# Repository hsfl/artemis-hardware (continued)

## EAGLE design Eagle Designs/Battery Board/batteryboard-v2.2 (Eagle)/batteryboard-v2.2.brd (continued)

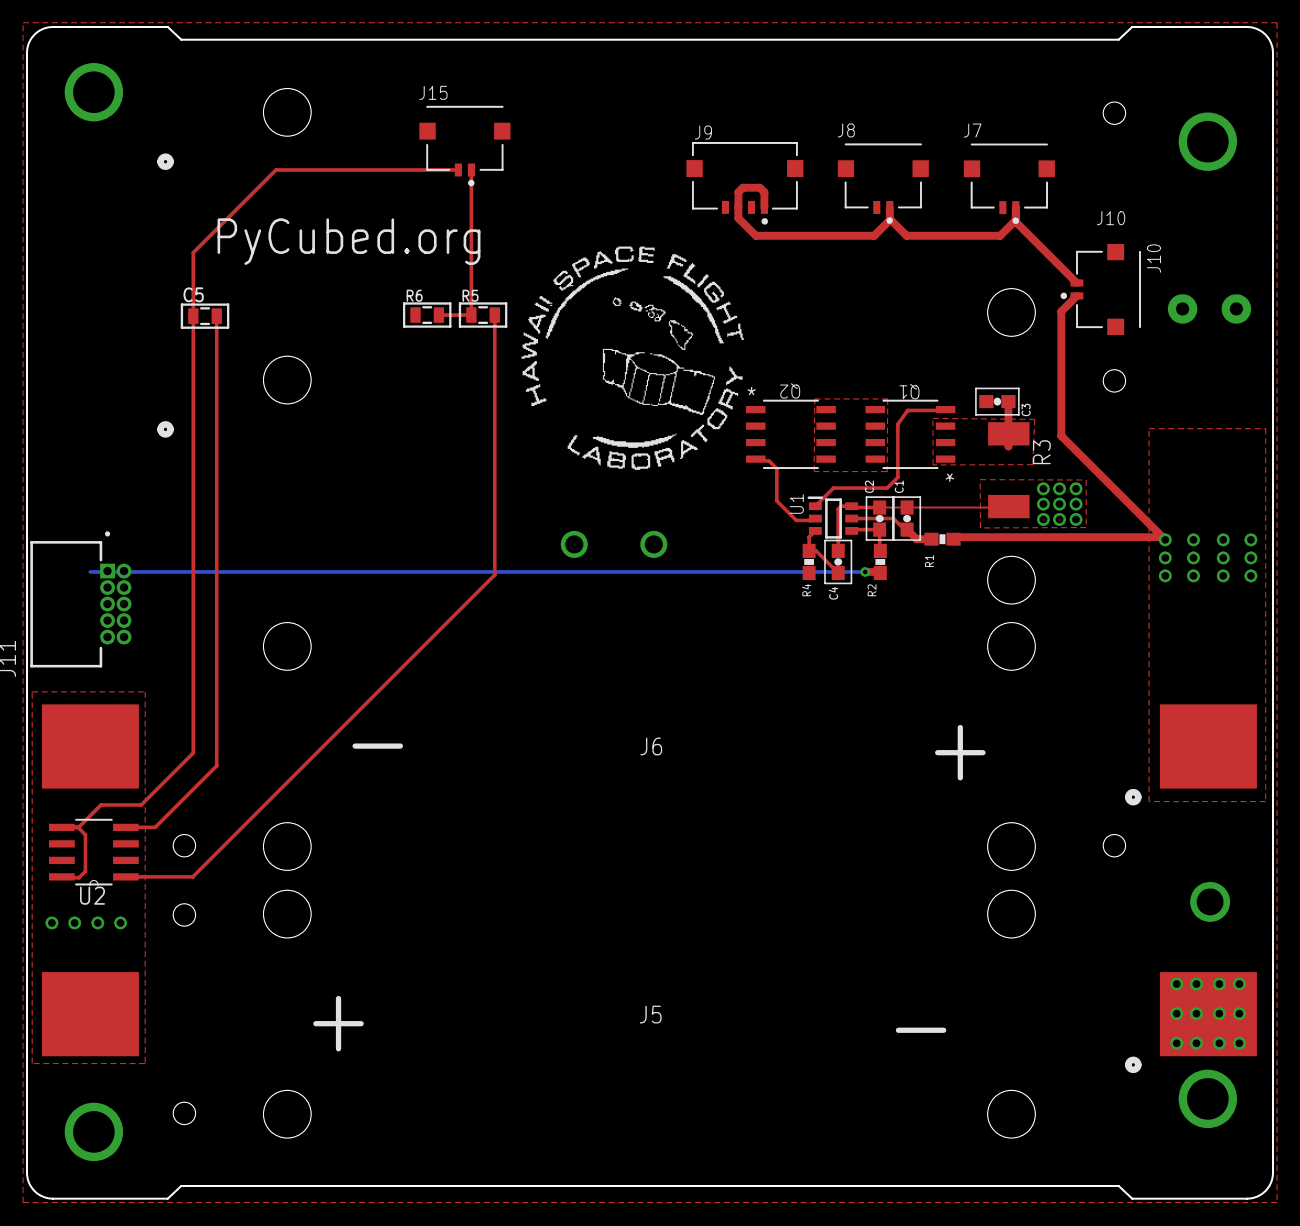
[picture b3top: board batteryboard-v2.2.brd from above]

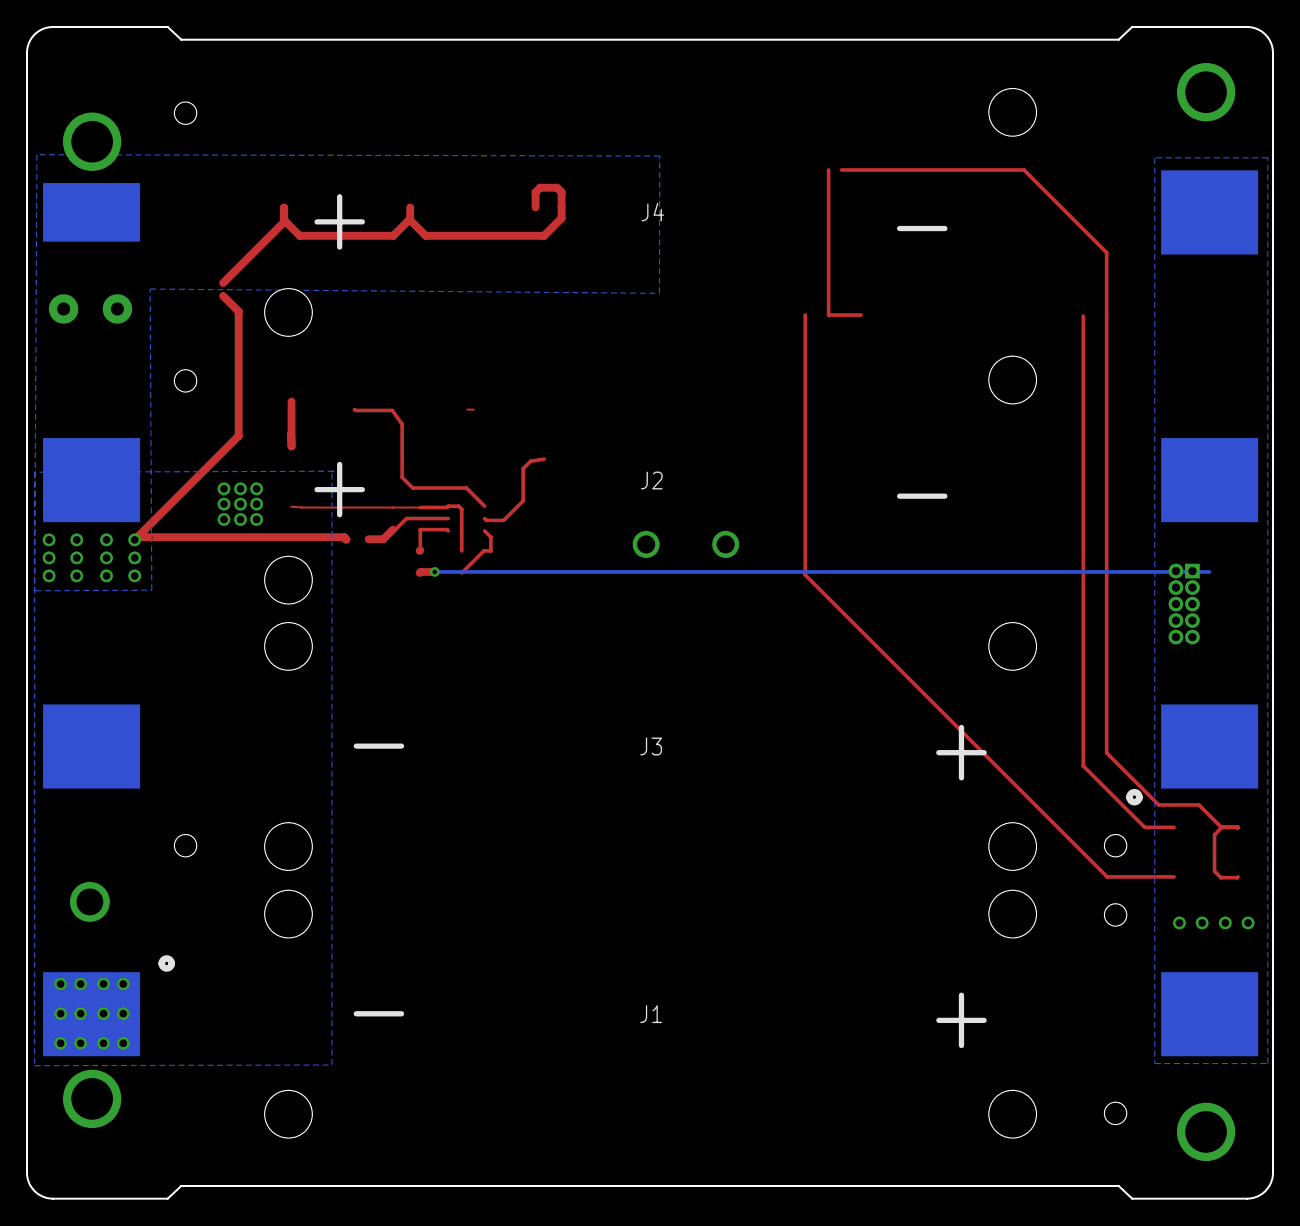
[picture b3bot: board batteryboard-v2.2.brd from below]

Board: 2 copper layers, 95.9 x 90.2 mm, 28 parts (4 on the bottom side), 16 nets.

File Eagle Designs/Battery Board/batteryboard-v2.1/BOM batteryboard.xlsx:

Id | Designator | Package | Quantity | Designation | Supplier and ref | Column1 | _1
1 | R6 | R_0805_2012Metric | 1 | 10k
2 | R5 | R_0805_2012Metric | 1 | 45.3k
3 | J2,J4,J6,J5,J3,J1 | KEYSTONE-1042 | 6 | KEYSTONE-1042
4 | Ref** | battery_version | 1 | Val**
5 | H3,H4,H2,H1 | MountingHole_3.2mm_M3_DIN965_PadMOD | 4 | MountingHole_Pad
6 | Ref** | pycubed_logo | 1 | Val**
7 | REF**,REF**,REF**,REF**,REF**,REF** | Fiducial_0.75mm_Mask1.5mm | 6 | Fiducial_0.75mm_Mask1.5mm
8 | TH1 | R_Axial_DIN0204_L3.6mm_D1.6mm_P5.08mm_Vertical | 1 | Thermistor
9 | J12 | PinHeader_1x01_P1.00mm_Vertical | 1 | Screw_Terminal_01x01
10 | TP4,TP3,TP2,TP1 | TestPoint_Loop_D1.80mm_Drill1.0mm_Beaded | 4 | TestPoint
11 | C3,C4,C2,C1,C5 | C_0603_1608Metric | 4 | 0.1uF
12 | R4 | R_0603_1608Metric | 1 | 1K
13 | R2,R1 | R_0603_1608Metric | 2 | 330
14 | R3 | R_2512_6332Metric | 1 | 0.01
15 | Q2,Q1 | SOIC-8_3.9x4.9mm_P1.27mm | 2 | IRF7458
16 | U1 | SOT95P280X130-6N | 1 | R5460N233AF
17 | J7,J8,J10 | Molex_Pico-Lock_503763-0291_1x02-1MP_P1.00m_Horizontal | 3 | Conn_01x02_Female
18 | J9,J11 | Molex_Pico-Lock_503763-0491_1x04-1MP_P1.00mm_Horizontal | 2 | Conn_01x04_Female
19 | U2 | TMP36FSZ-REEL | 1 | TMP36FSZ-REEL

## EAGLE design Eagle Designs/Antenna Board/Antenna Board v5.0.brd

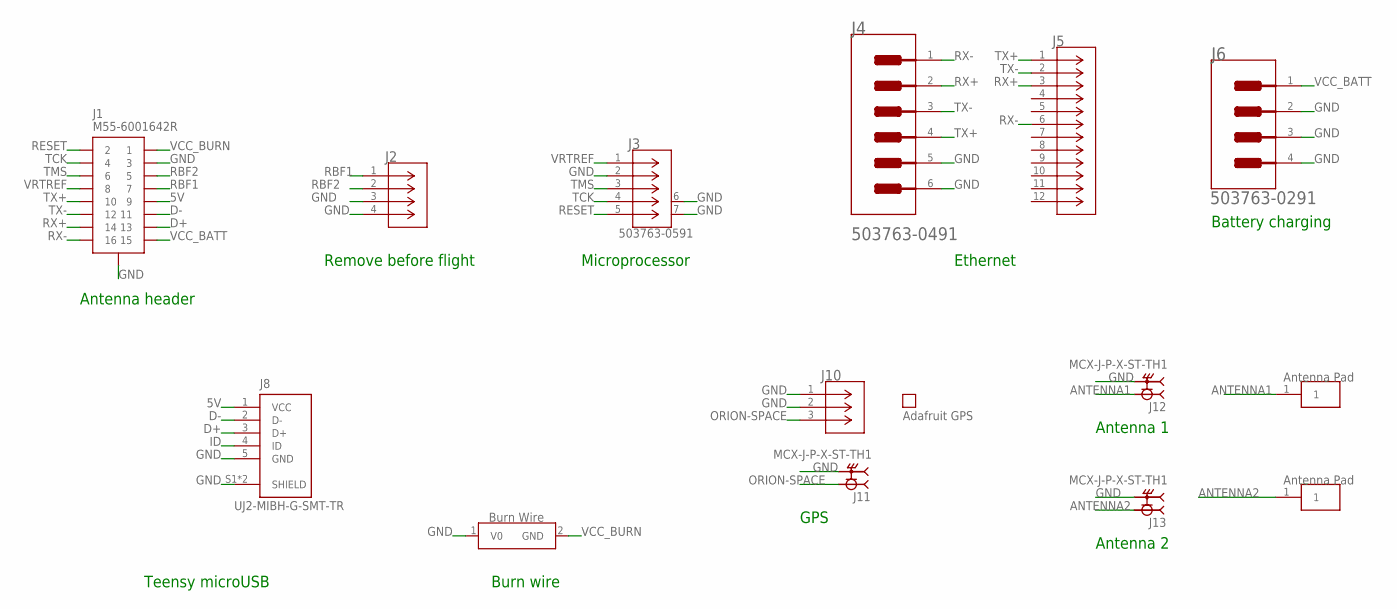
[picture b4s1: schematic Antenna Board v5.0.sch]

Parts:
GPS: PA1010D
J1: M55-6001642R; CONN_M55-6001642R_HRW
J2: 5037630291; CON_5037630291
J3: 503763-0591; CONN_5037630591_MOL
J4: MOLEX_503763-0491MOLEX_503763-0491_0_0; MOLEX_503763-0491_0
J5: ARJM11C7-104-AB-EW2; CONN_EW_ABR
J6: MOLEX_503763-0291MOLEX_503763-0291_0_0; MOLEX_503763-0291_0
J8: UJ2-MIBH-G-SMT-TR; CUI_UJ2-MIBH-G-SMT-TR
J10: U.FL-R-SMT-1(01); CONN_-SMT-1(01)
J11, J12, J13: MCX-J-P-X-ST-TH1; SAMTEC_MCX-J-P-X-ST-TH1
U$1, U$2: ANTENNA_PAD
U$3: BURNWIRE

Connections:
5V: J1.9, J8.1 (VCC)
ANTENNA1: J12.1, U$2.1
ANTENNA2: J13.1, U$1.1
D+: J1.13, J8.3 (D+)
D-: J1.11, J8.2 (D-)
GND: J1.3, J1.19 (GND), J1.20 (GND), J1.21 (GND), J1.22 (GND), J2.3, J2.4, J3.2, J3.6, J3.7, J4.5 (MNT_1), J4.6 (MNT_2), J6.2, J6.3 (MNT_1), J6.4 (MNT_2), J8.5 (GND), J8.S1 (SHIELD), J8.S2 (SHIELD), J10.1, J10.2, J11.S1 (2), J11.S2 (2), J11.S3 (2), J11.S4 (2), J12.S1 (2), J12.S2 (2), J12.S3 (2), J12.S4 (2), J13.S1 (2), J13.S2 (2), J13.S3 (2), J13.S4 (2), U$3.1 (V0)
ID: J8.4 (ID)
ORION-SPACE: J10.3, J11.1
RBF1: J1.7, J2.1
RBF2: J1.5, J2.2
RESET: J1.2, J3.5
RX+: J1.14, J4.2, J5.3
RX-: J1.16, J4.1, J5.6
TCK: J1.4, J3.4
TMS: J1.6, J3.3
TX+: J1.10, J4.4, J5.1
TX-: J1.12, J4.3, J5.2
VCC_BATT: J1.15, J6.1
VCC_BURN: J1.1, U$3.2 (GND)
VRTREF: J1.8, J3.1

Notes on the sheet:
Remove before flight
Microprocessor
Battery charging
Teensy microUSB
Burn wire
GPS
Antenna 1
Antenna 2
Ethernet
Antenna header

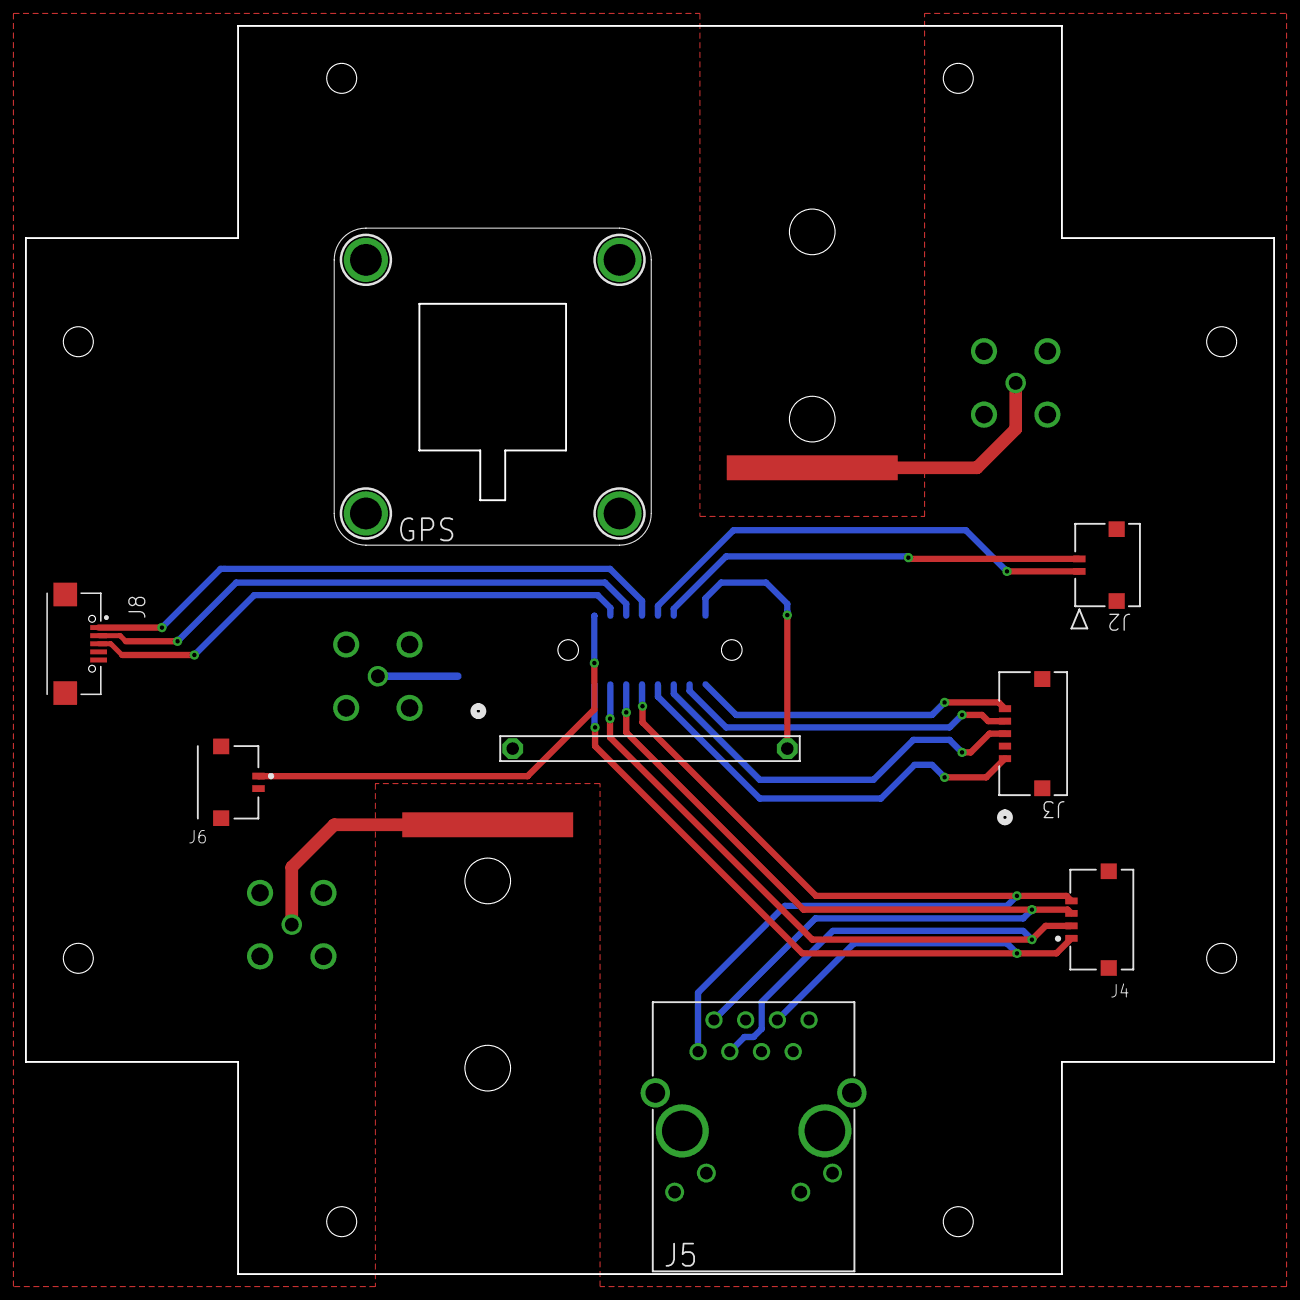
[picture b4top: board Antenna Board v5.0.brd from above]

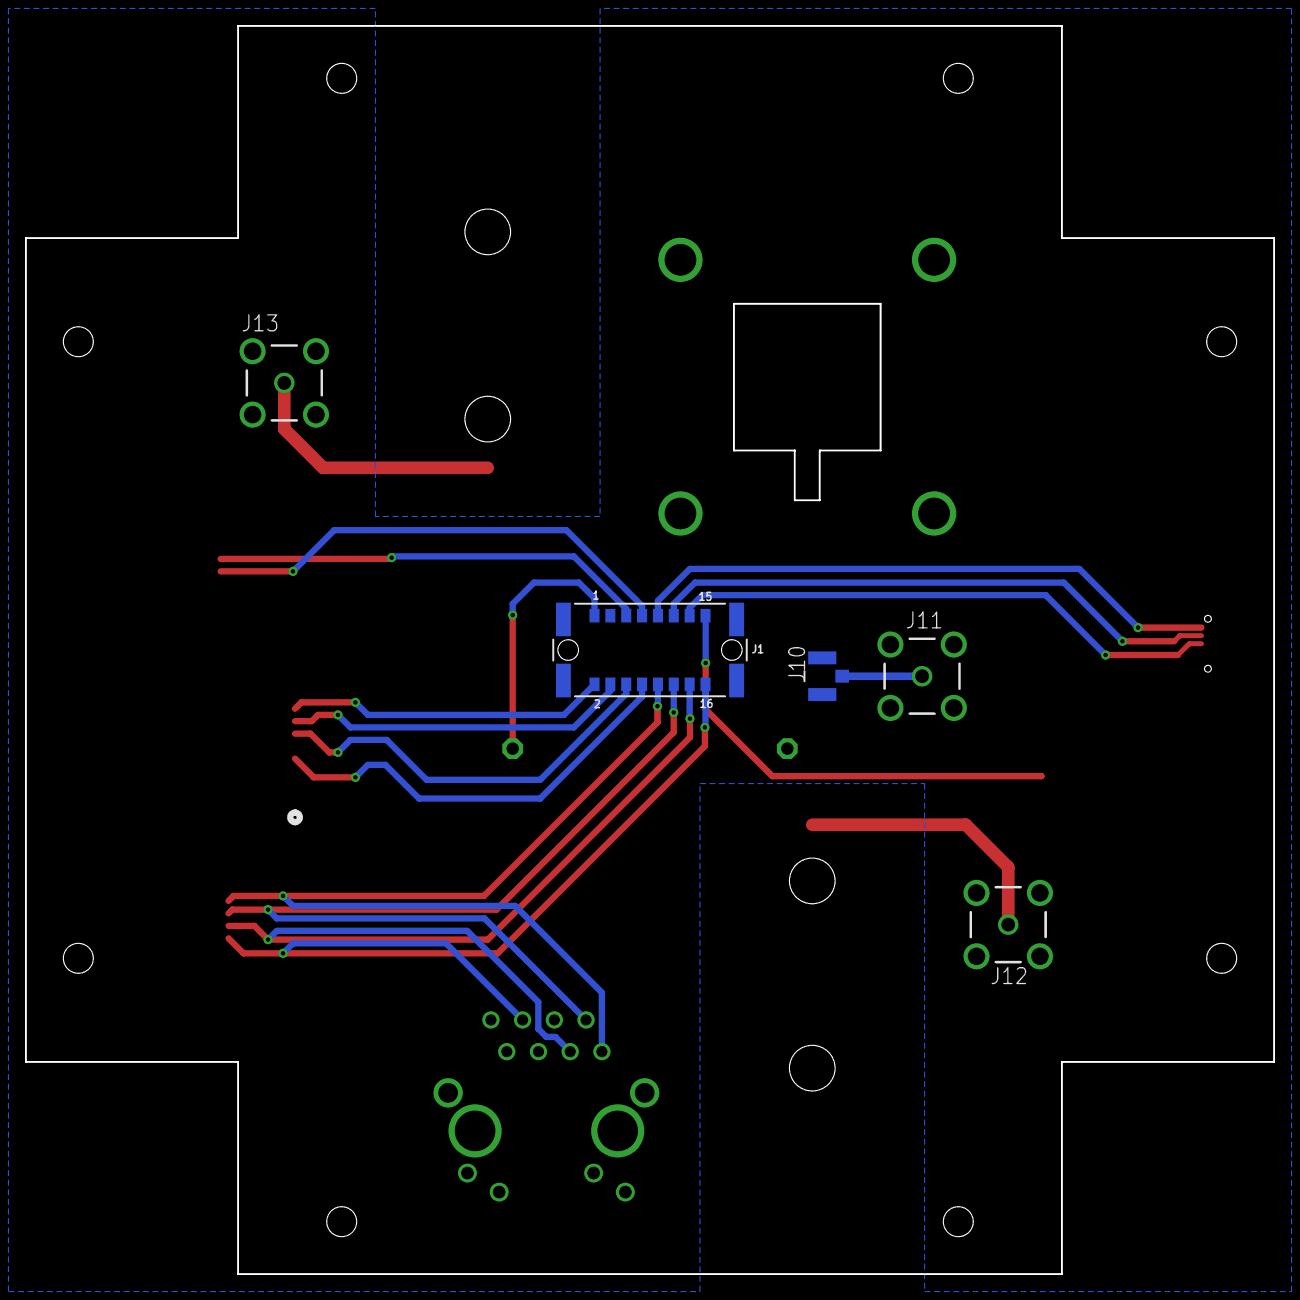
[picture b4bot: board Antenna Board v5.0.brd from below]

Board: 2 copper layers, 100.0 x 100.0 mm, 15 parts (5 on the bottom side), 19 nets.

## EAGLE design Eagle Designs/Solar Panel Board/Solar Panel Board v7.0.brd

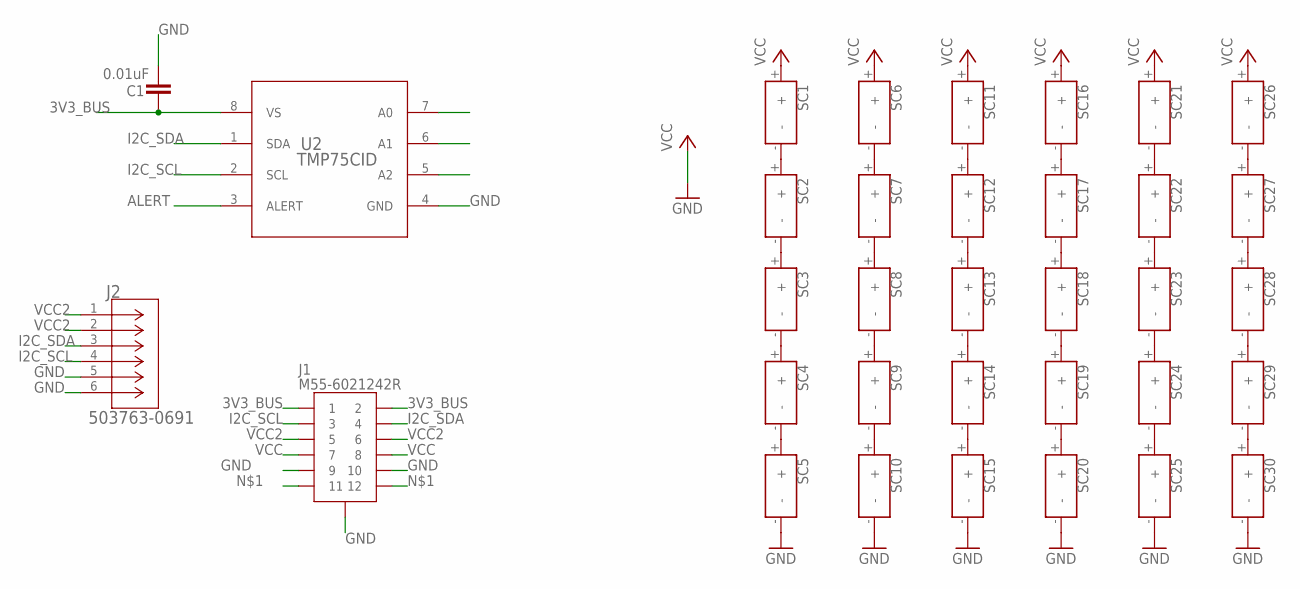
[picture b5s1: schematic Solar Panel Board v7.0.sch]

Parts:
C1: 0.01uF; 0805
J1: M55-6021242R
J2: 503763-0691; CONN_503763-0691_MOL
SC1, SC2, SC3, SC4, SC5, SC6, SC7, SC8, SC9, SC10, SC11, SC12, SC13, SC14, SC15, SC16, SC17, SC18, SC19, SC20, SC21, SC22, SC23, SC24, SC25, SC26, SC27, SC28, SC29, SC30: KXOB25-05X3F
U2: TMP75CID; D0008A_N

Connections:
3V3_BUS: C1.1, J1.1, J1.2, U2.8 (VS)
ALERT: U2.3 (ALERT)
GND: C1.2, J1.9, J1.10, J1.P$1 (GND), J1.P$2 (GND), J1.P$3 (GND), J1.P$4 (GND), J2.5, J2.6, SC5.-, SC10.-, SC15.-, SC20.-, SC25.-, SC30.-, U2.4 (GND)
I2C_SCL: J1.3, J2.4, U2.2 (SCL)
I2C_SDA: J1.4, J2.3, U2.1 (SDA)
unnamed: J1.11, J1.12
unnamed: SC7.-, SC8.+
unnamed: SC4.-, SC5.+
unnamed: SC3.-, SC4.+
unnamed: SC2.-, SC3.+
unnamed: SC1.-, SC2.+
unnamed: SC8.-, SC9.+
unnamed: SC16.-, SC17.+
unnamed: SC14.-, SC15.+
unnamed: SC13.-, SC14.+
unnamed: SC9.-, SC10.+
unnamed: SC11.-, SC12.+
unnamed: SC23.-, SC24.+
unnamed: SC22.-, SC23.+
unnamed: SC21.-, SC22.+
unnamed: SC6.-, SC7.+
unnamed: SC17.-, SC18.+
unnamed: SC19.-, SC20.+
unnamed: SC12.-, SC13.+
unnamed: SC28.-, SC29.+
unnamed: SC29.-, SC30.+
unnamed: SC26.-, SC27.+
unnamed: SC24.-, SC25.+
unnamed: SC18.-, SC19.+
unnamed: SC27.-, SC28.+
VCC: J1.7, J1.8, SC1.+, SC6.+, SC11.+, SC16.+, SC21.+, SC26.+
VCC2: J1.5, J1.6, J2.1, J2.2

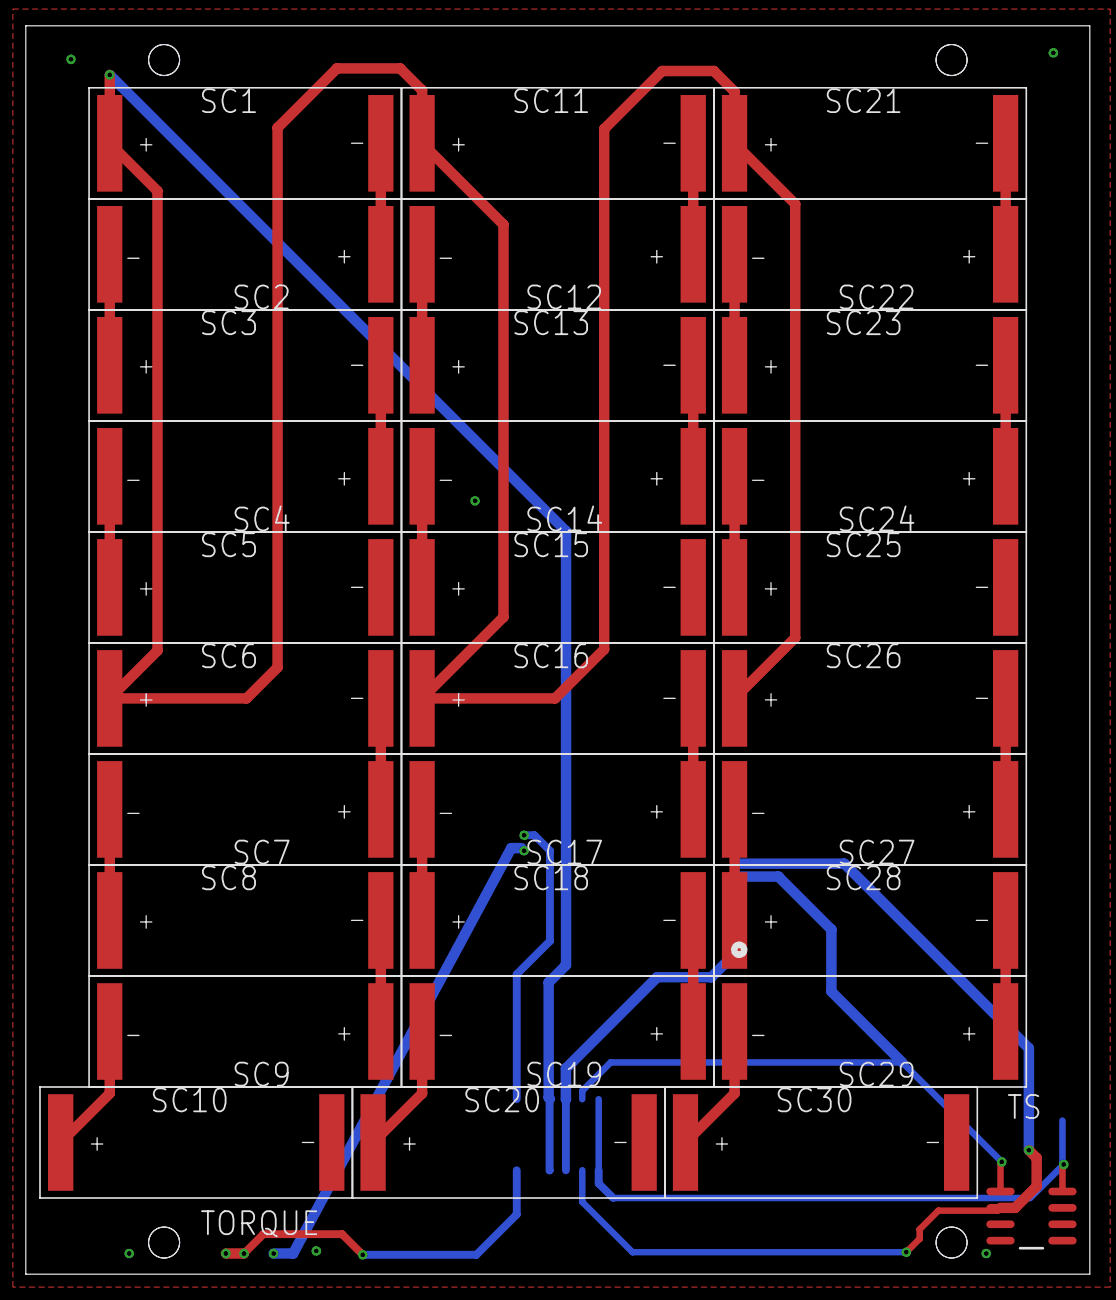
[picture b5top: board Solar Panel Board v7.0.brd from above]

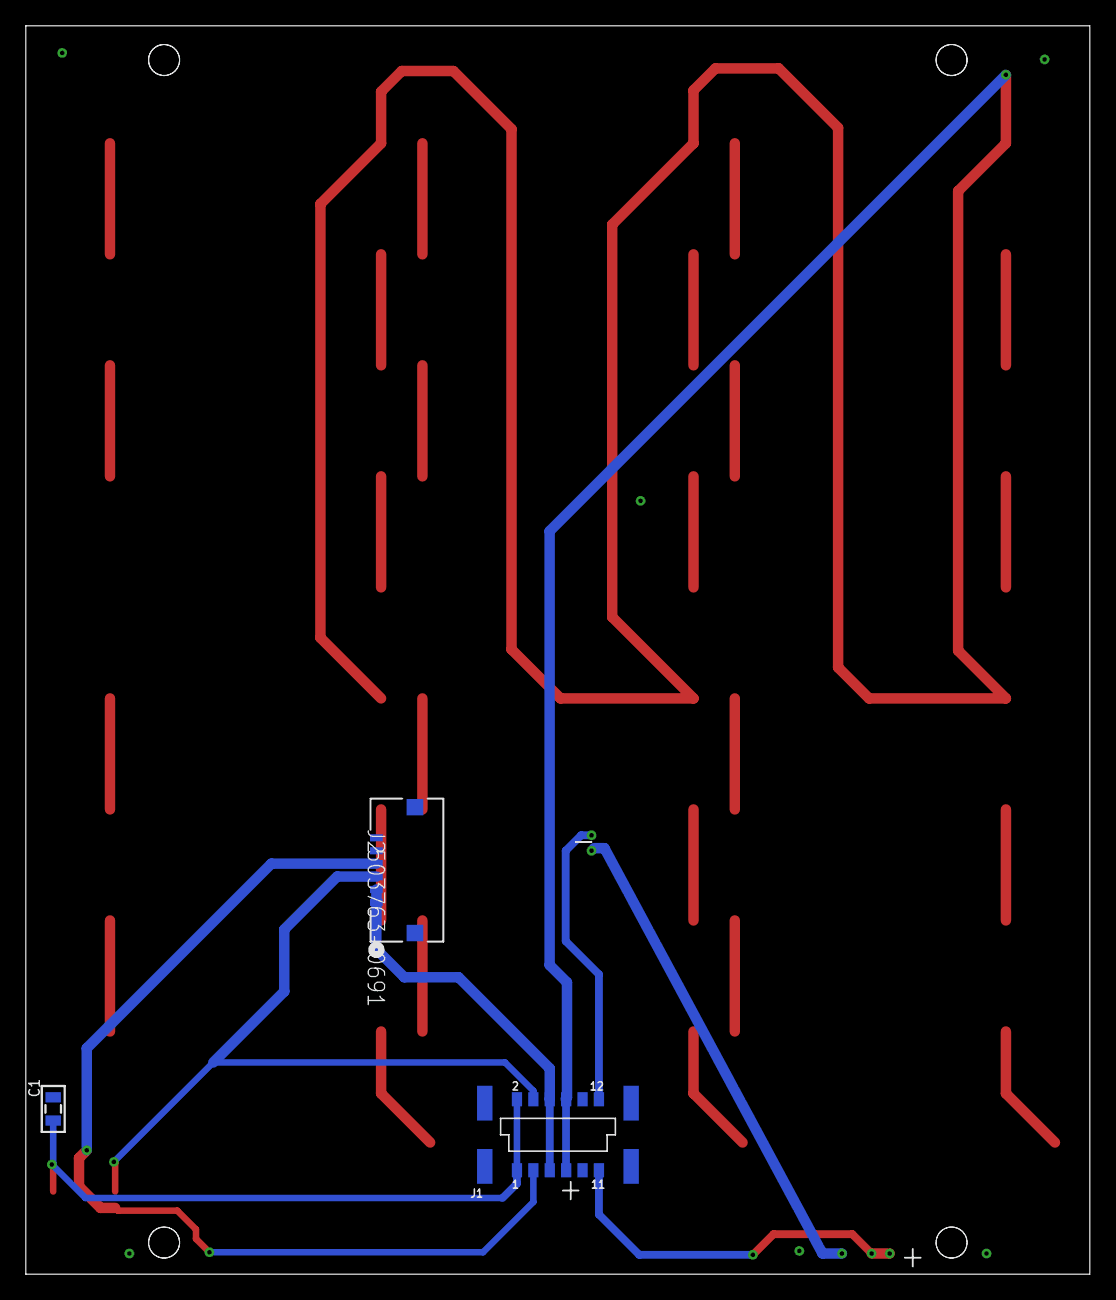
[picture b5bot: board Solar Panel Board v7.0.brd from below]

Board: 4 copper layers, 82.4 x 96.7 mm, 34 parts (3 on the bottom side), 31 nets.

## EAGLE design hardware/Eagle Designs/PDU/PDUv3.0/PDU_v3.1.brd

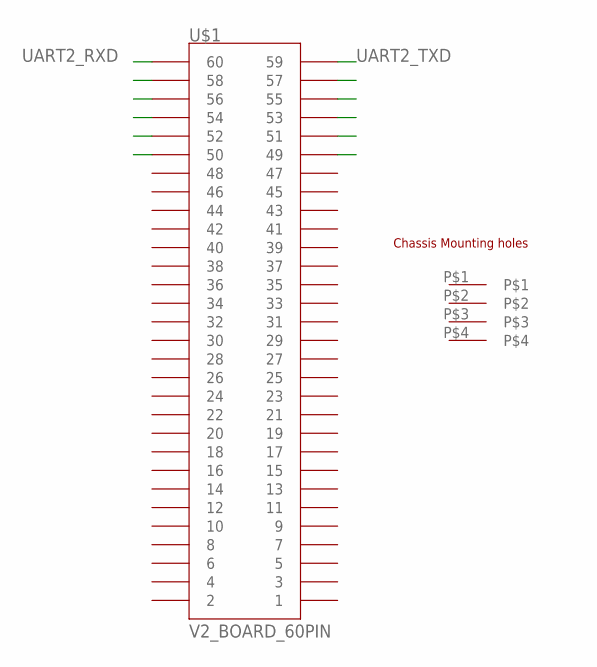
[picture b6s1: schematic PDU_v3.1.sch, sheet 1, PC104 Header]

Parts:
U$1: V2_BOARD_60PIN; PC104_WCONN_BACKPLANE_HEADER

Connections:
UART2_RXD: U$1.60; also elsewhere on the board
UART2_TXD: U$1.59; also elsewhere on the board

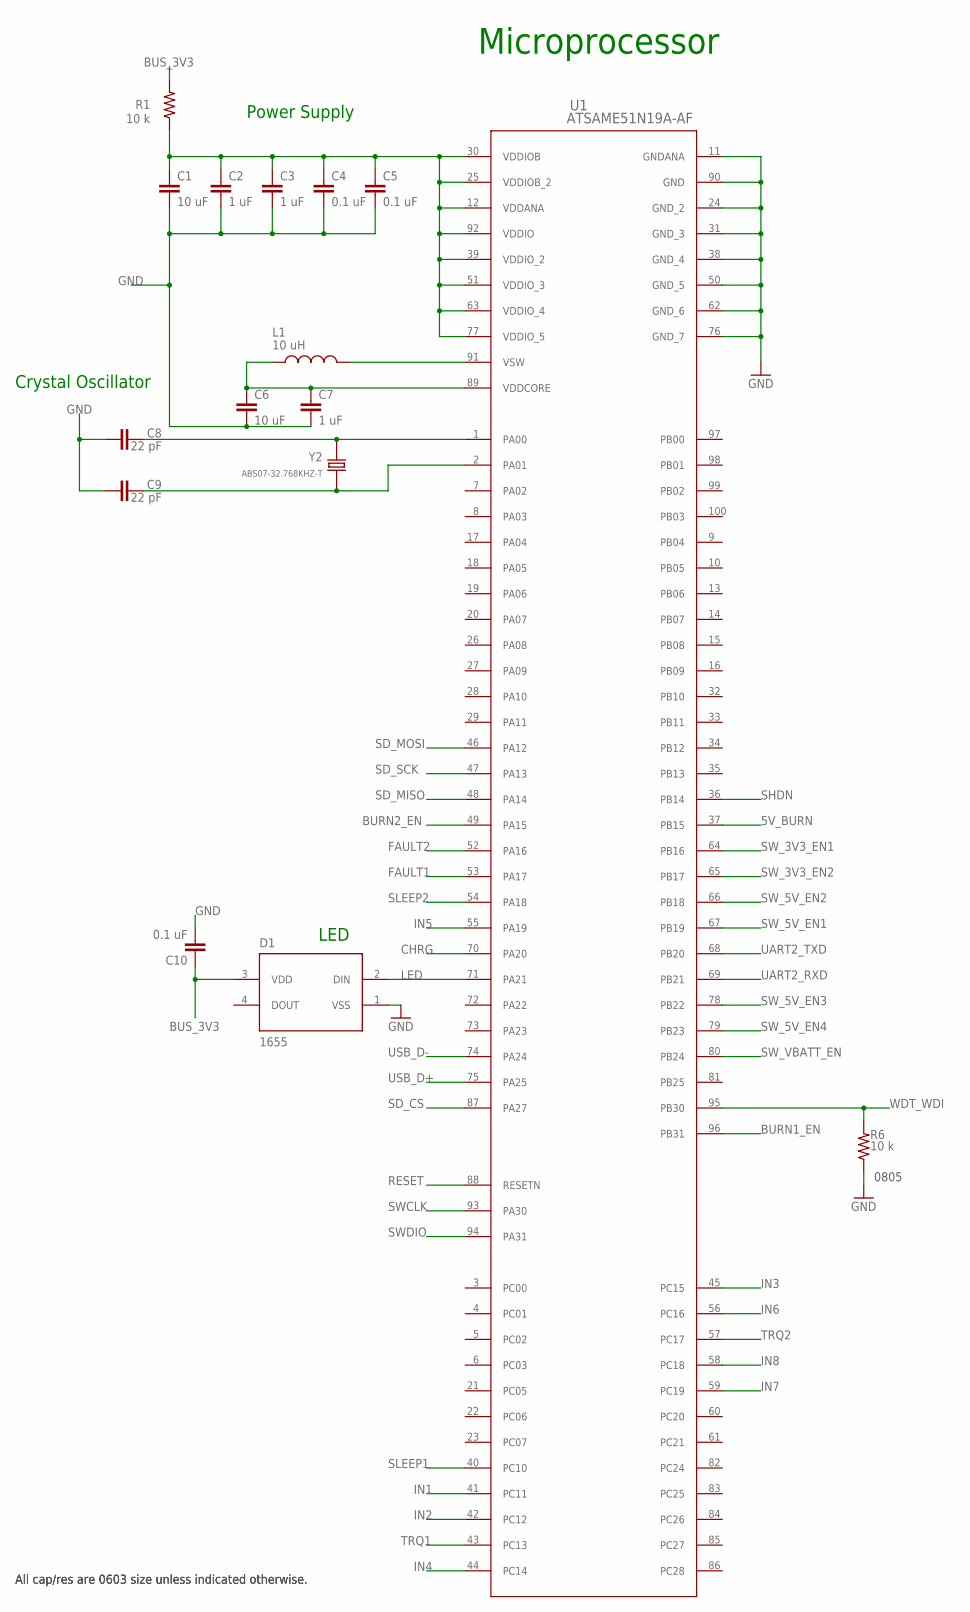
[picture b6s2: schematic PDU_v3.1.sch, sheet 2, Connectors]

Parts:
C1, C6: 10 uF; 0603-CAP
C2, C3, C7: 1 uF; 0603-CAP
C4, C5, C10: 0.1 uF; 0603-CAP
C8, C9: 22 pF; 0603-CAP
D1: 1655; LED_1655
L1: 10 uH; INDC2012X100N
R1: 10 k; 0603-RES
R6: 10 k; 0805
U1: ATSAME51N19A-AF; TQFP100_14X14MC_MCH
Y2: ABS07-32.768KHZ-T; XTAL_ABS07-32.768KHZ-T

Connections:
5V_BURN: U1.37 (PB15)
BURN1_EN: U1.96 (PB31)
BURN2_EN: U1.49 (PA15)
BUS_3V3: C10.1, D1.3 (VDD), R1.2
CCO_2: C8.2, U1.1 (PA00), Y2.2
CCO_3: C9.2, U1.2 (PA01), Y2.1
CHRG: U1.70 (PA20)
FAULT1: U1.53 (PA17)
FAULT2: U1.52 (PA16)
GND: C1.2, C2.2, C3.2, C4.2, C5.2, C6.2, C7.2, C8.1, C9.1, C10.2, D1.1 (VSS), R6.1, U1.11 (GNDANA), U1.24 (GND_2), U1.31 (GND_3), U1.38 (GND_4), U1.50 (GND_5), U1.62 (GND_6), U1.76 (GND_7), U1.90 (GND); also elsewhere on the board
IN1: U1.41 (PC11)
IN2: U1.42 (PC12)
IN3: U1.45 (PC15)
IN4: U1.44 (PC14)
IN5: U1.55 (PA19)
IN6: U1.56 (PC16)
IN7: U1.59 (PC19)
IN8: U1.58 (PC18)
LED: D1.2 (DIN), U1.71 (PA21)
unnamed: C6.1, C7.1, L1.1, U1.89 (VDDCORE)
unnamed: L1.2, U1.91 (VSW)
RESET: U1.88 (RESETN)
SD_CS: U1.87 (PA27)
SD_MISO: U1.48 (PA14)
SD_MOSI: U1.46 (PA12)
SD_SCK: U1.47 (PA13)
SHDN: U1.36 (PB14)
SLEEP1: U1.40 (PC10)
SLEEP2: U1.54 (PA18)
SWCLK: U1.93 (PA30)
SWDIO: U1.94 (PA31)
SW_3V3_EN1: U1.64 (PB16)
SW_3V3_EN2: U1.65 (PB17)
SW_5V_EN1: U1.67 (PB19)
SW_5V_EN2: U1.66 (PB18)
SW_5V_EN3: U1.78 (PB22)
SW_5V_EN4: U1.79 (PB23)
SW_VBATT_EN: U1.80 (PB24)
TRQ1: U1.43 (PC13)
TRQ2: U1.57 (PC17)
UART2_RXD: U1.69 (PB21); also elsewhere on the board
UART2_TXD: U1.68 (PB20); also elsewhere on the board
USB_D+: U1.75 (PA25)
USB_D-: U1.74 (PA24)
VDD2: C1.1, C2.1, C3.1, C4.1, C5.1, R1.1, U1.12 (VDDANA), U1.25 (VDDIOB_2), U1.30 (VDDIOB), U1.39 (VDDIO_2), U1.51 (VDDIO_3), U1.63 (VDDIO_4), U1.77 (VDDIO_5), U1.92 (VDDIO)
WDT_WDI: R6.2, U1.95 (PB30)

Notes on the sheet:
Microprocessor
LED
Power Supply
Crystal Oscillator
0805
All cap/res are 0603 size unless indicated otherwise.

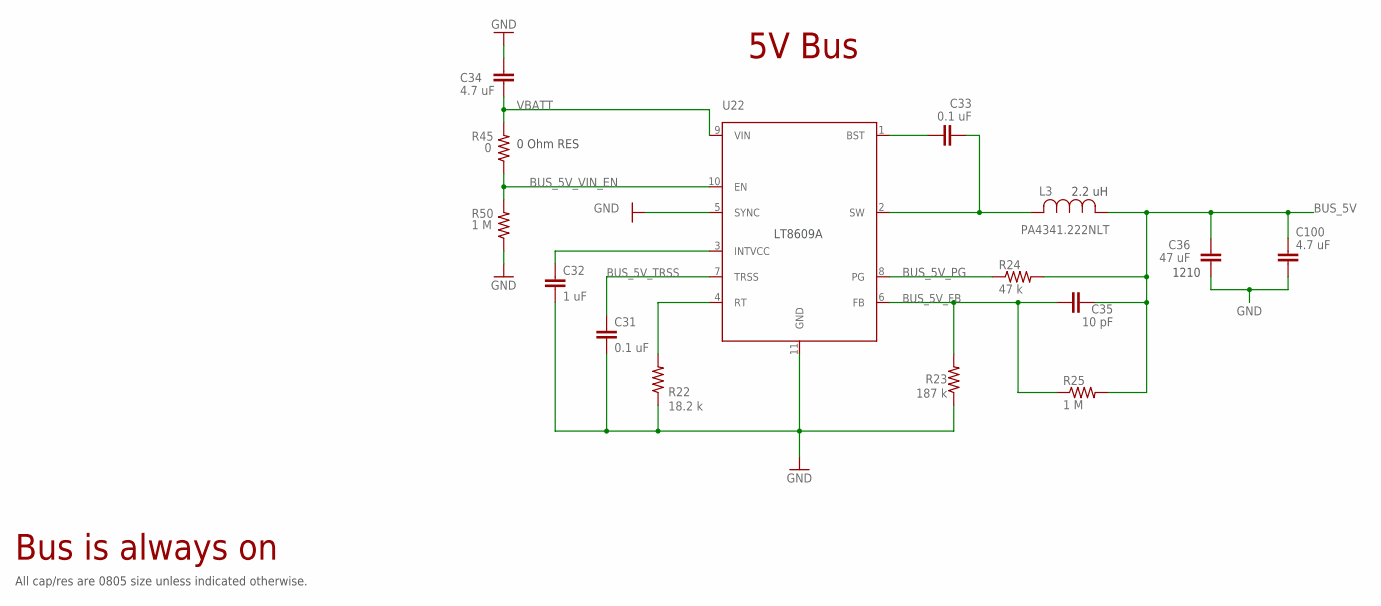
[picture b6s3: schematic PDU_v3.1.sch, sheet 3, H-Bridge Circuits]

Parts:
C31, C33: 0.1 uF; 0805
C32: 1 uF; 0805
C34, C100: 4.7 uF; 0805
C35: 10 pF; 0805
C36: 47 uF; 1210
L3: PA4341.222NLT; IND_222NLT_PUL
R22: 18.2 k; 0805
R23: 187 k; 0805
R24: 47 k; 0805
R25, R50: 1 M; 0805
R45: 0; 0805
U22: LT8609A; MSOP-10_MSE

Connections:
BUS_5V: C35.2, C36.1, C100.1, L3.1, R24.2, R25.2
BUS_5V_FB: C35.1, R23.2, R25.1, U22.6 (FB)
BUS_5V_PG: R24.1, U22.8 (PG)
BUS_5V_TRSS: C31.1, U22.7 (TRSS)
BUS_5V_VIN_EN: R45.1, R50.2, U22.10 (EN)
GND: C31.2, C32.2, C34.2, C36.2, C100.2, R22.1, R23.1, R50.1, U22.5 (SYNC), U22.11 (GND); also elsewhere on the board
unnamed: R22.2, U22.4 (RT)
unnamed: C32.1, U22.3 (INTVCC)
unnamed: C33.1, U22.1 (BST)
unnamed: C33.2, L3.2, U22.2 (SW)
VBATT: C34.1, R45.2, U22.9 (VIN)

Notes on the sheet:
Bus is always on
All cap/res are 0805 size unless indicated otherwise.
0 Ohm RES
5V Bus
2.2 uH
1210

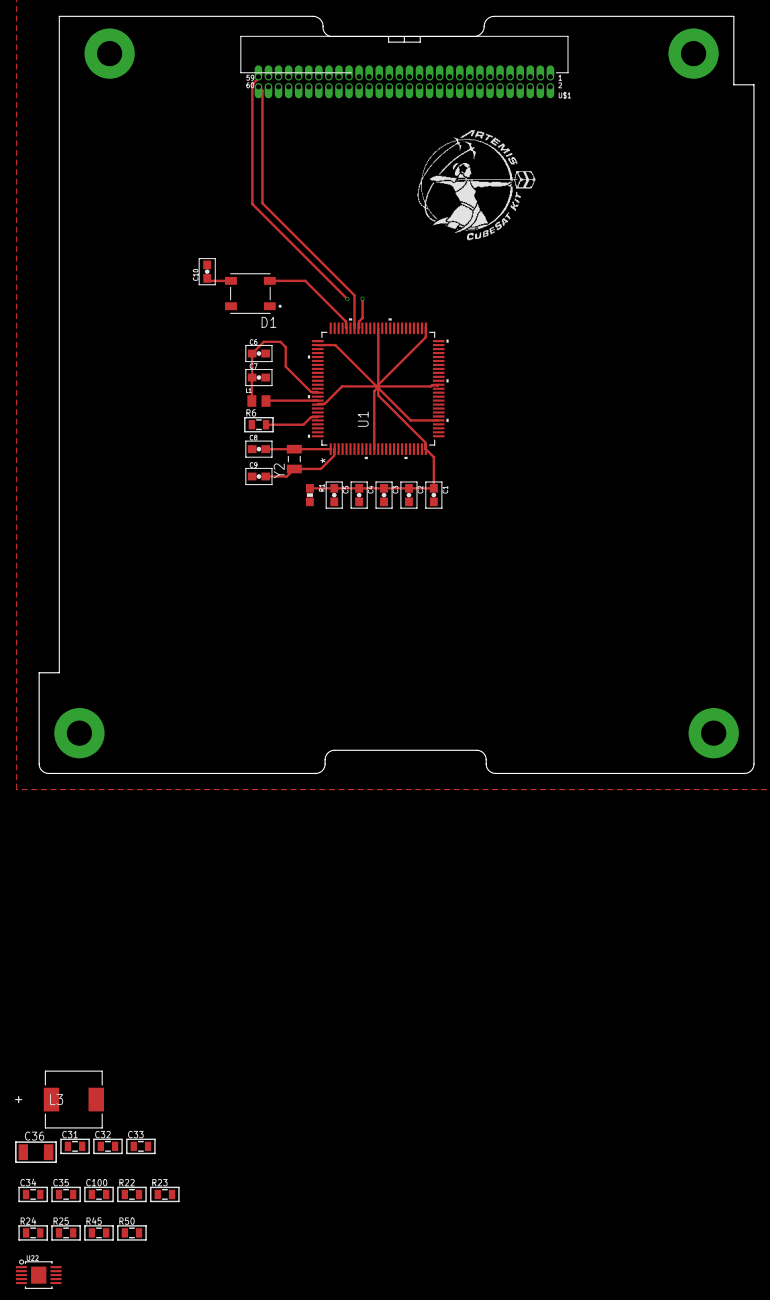
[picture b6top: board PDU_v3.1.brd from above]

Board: 4 copper layers, 90.2 x 95.5 mm, 32 parts (0 on the bottom side), 21 nets.

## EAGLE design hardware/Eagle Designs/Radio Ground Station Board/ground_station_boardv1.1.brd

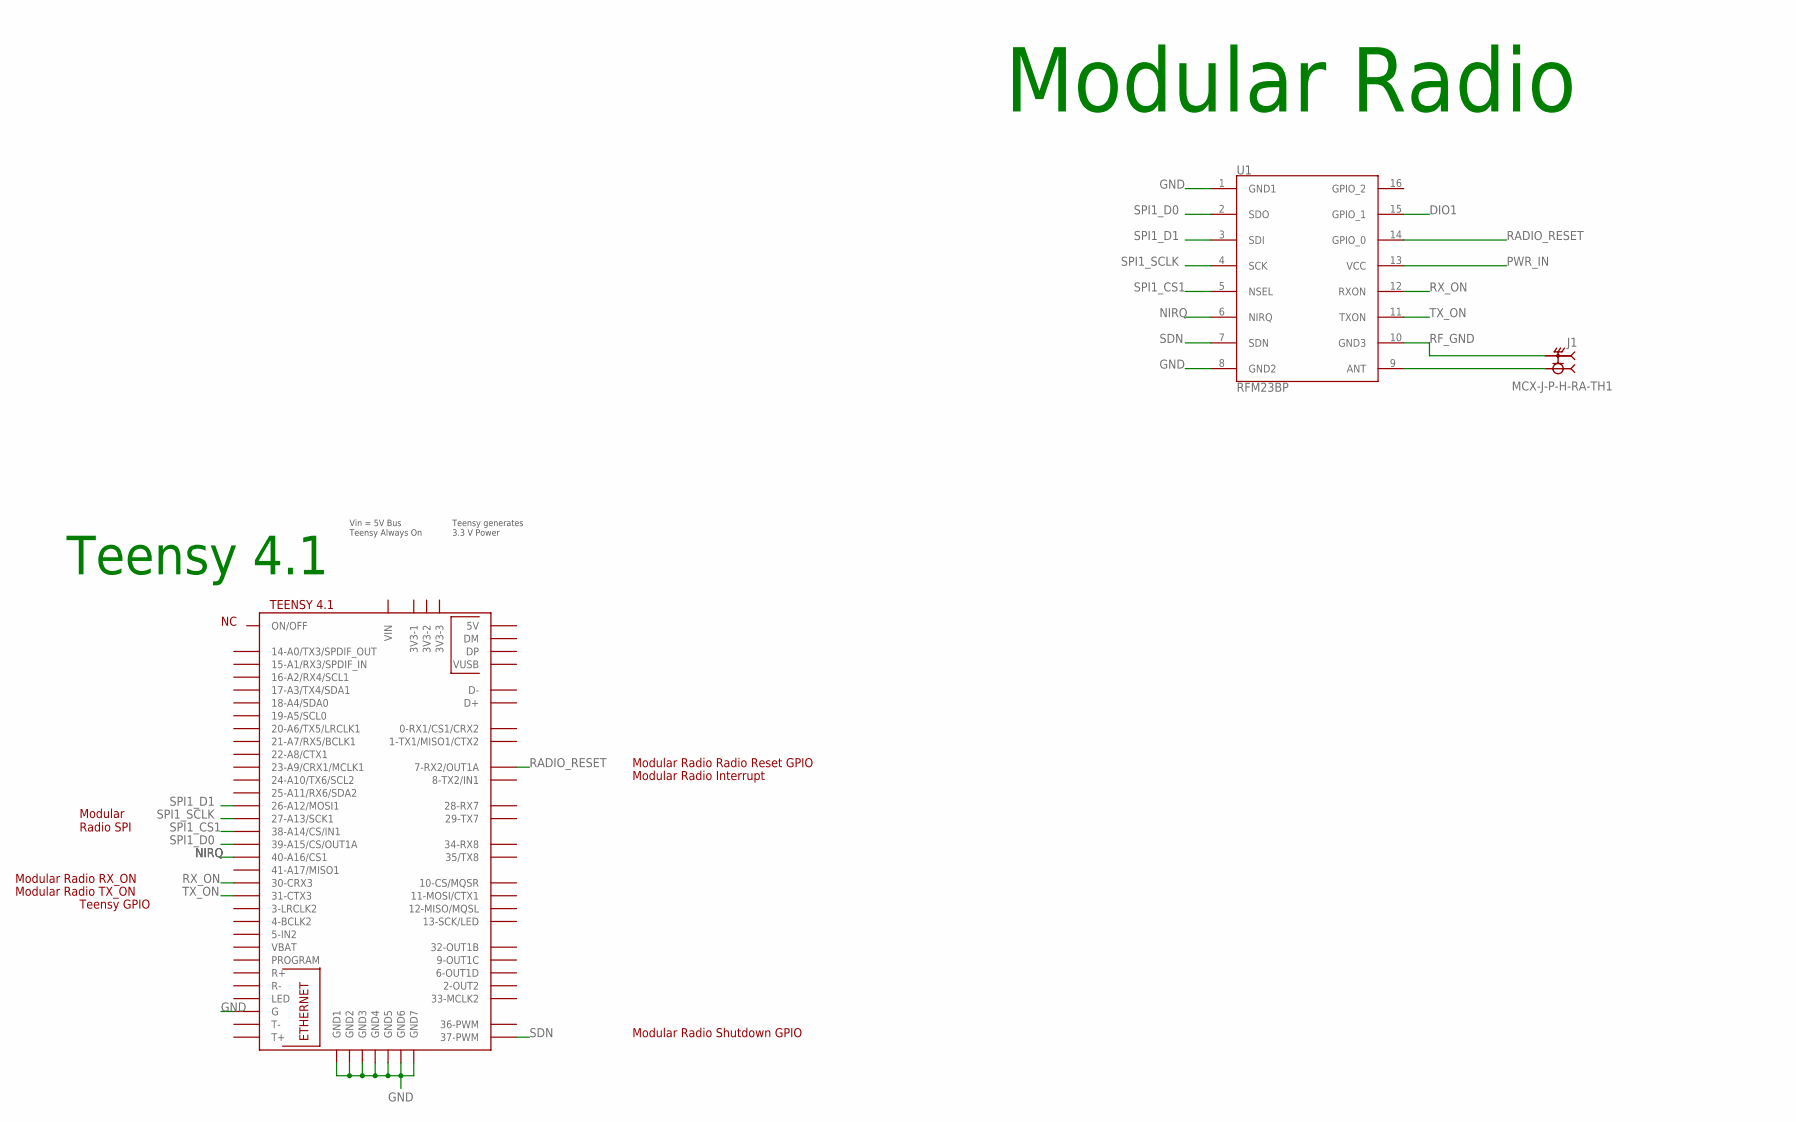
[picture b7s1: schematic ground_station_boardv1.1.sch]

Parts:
J1: MCX-J-P-H-RA-TH1; SAMTEC_MCX-J-P-H-RA-TH1
U1: RFM23BP
U$1: TEENSY41TEENSY; TEENSY41

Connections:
DIO1: U1.15 (GPIO_1)
GND: U1.1 (GND1), U1.8 (GND2), U$1.G, U$1.GND (GND7), U$1.GND1, U$1.GND2, U$1.GND3, U$1.GND4, U$1.GND5, U$1.GND6
unnamed: J1.1, U1.9 (ANT)
NIRQ: U1.6 (NIRQ), U$1.40-A16/CS1
PWR_IN: U1.13 (VCC)
RADIO_RESET: U1.14 (GPIO_0), U$1.7-RX2/OUT1A
RF_GND: J1.S1 (2), J1.S2 (2), J1.S3 (2), J1.S4 (2), U1.10 (GND3)
RX_ON: U1.12 (RXON), U$1.30-CRX3
SDN: U1.7 (SDN), U$1.37-PWM
SPI1_CS1: U1.5 (NSEL), U$1.38-A14/CS/IN1
SPI1_D0: U1.2 (SDO), U$1.39-A15/CS/OUT1A
SPI1_D1: U1.3 (SDI), U$1.26-A12/MOSI1
SPI1_SCLK: U1.4 (SCK), U$1.27-A13/SCK1
TX_ON: U1.11 (TXON), U$1.31-CTX3

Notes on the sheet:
Teensy 4.1
Modular Radio SPI
Teensy GPIO
Modular Radio Radio Reset GPIO
Vin = 5V Bus Teensy Always On
Teensy generates 3.3 V Power
Modular Radio Interrupt
Modular Radio RX_ON
Modular Radio TX_ON
Modular Radio Shutdown GPIO
Modular Radio
